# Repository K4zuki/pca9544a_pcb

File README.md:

# pca9544a_pcb
a PCB design for PCA9544A I2C MUX

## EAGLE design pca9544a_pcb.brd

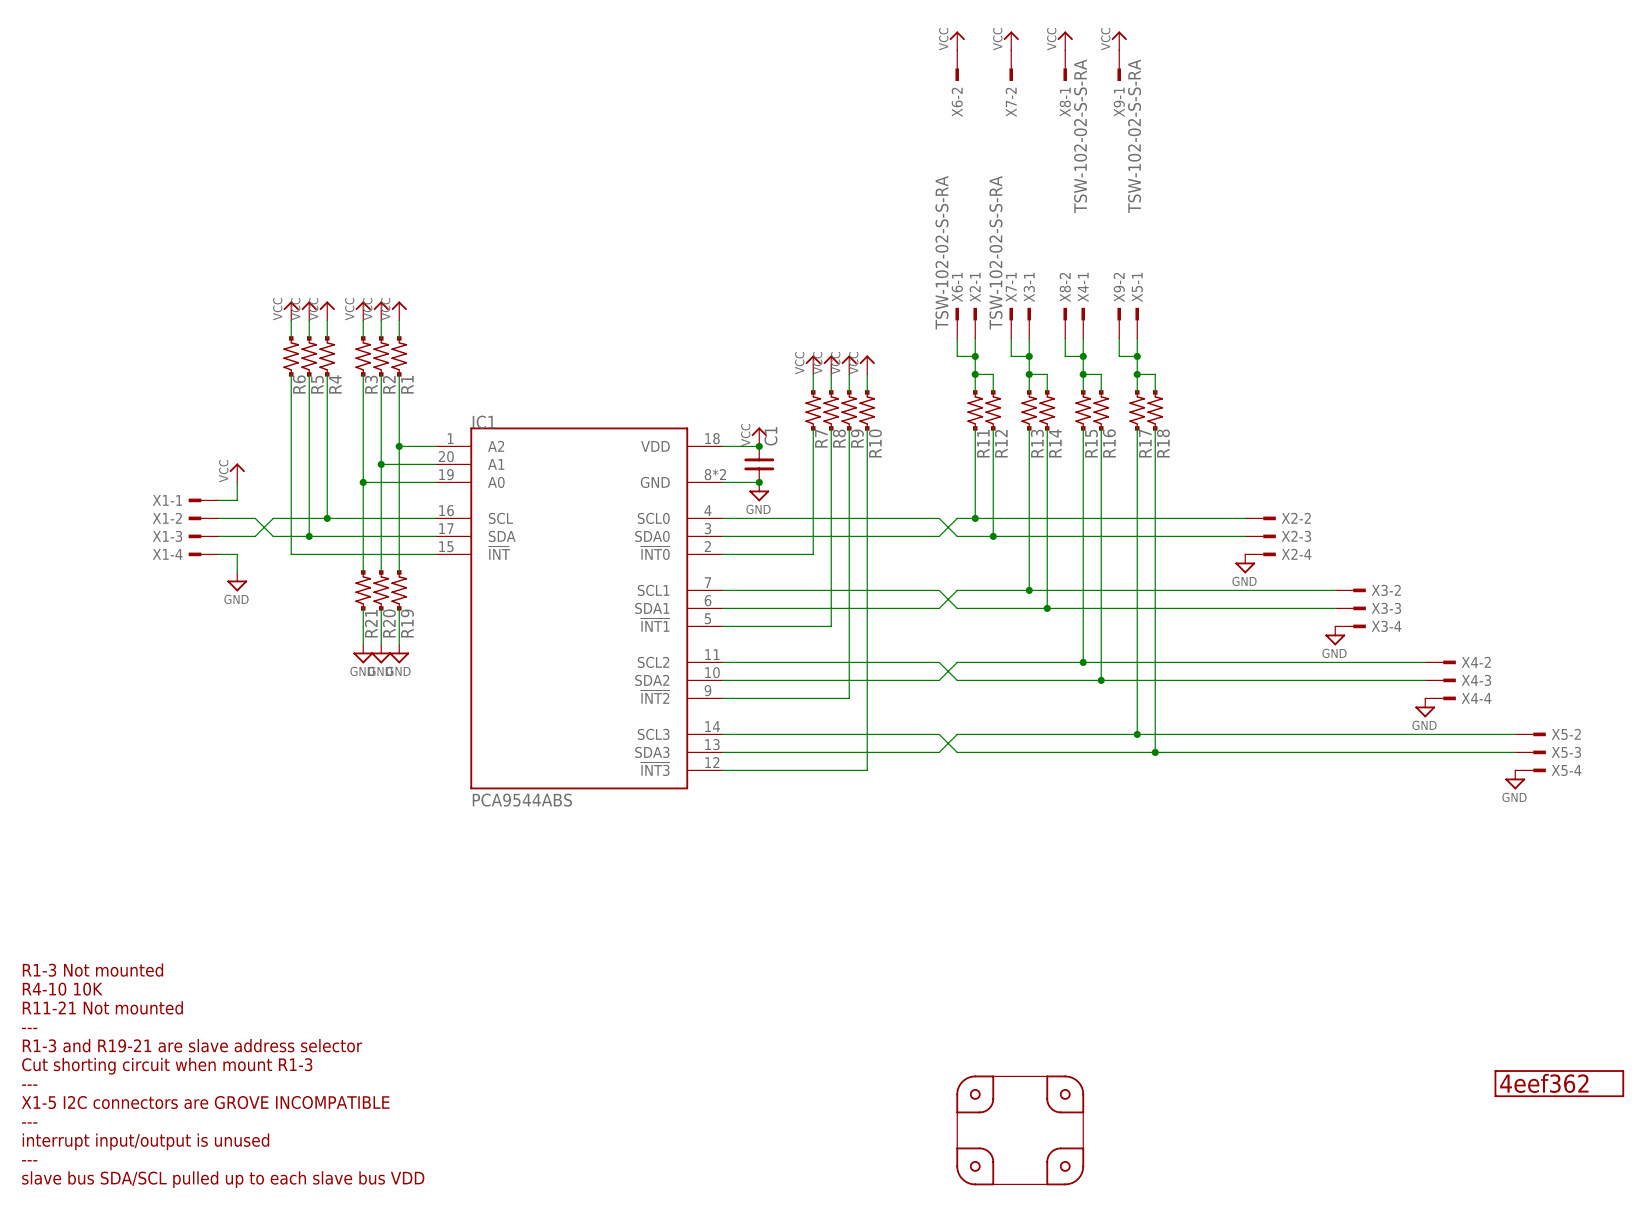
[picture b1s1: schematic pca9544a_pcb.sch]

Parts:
C1: C-SMD-0.1U-1608; CR-1608
GIT1: 4eef362; GIT-REVISION_1.2
IC1: PCA9544ABS; QFN20-0.65P5.0X5.0
P1, P2, P3, P4: PCB-CORNER
R1, R2, R3, R4, R5, R6, R7, R8, R9, R10, R11, R12, R13, R14, R15, R16, R17, R18: R-US-10K-1608; R-1608-PADPAD
R19, R20, R21: R-US--1005SHORT; R0402SHORT
X1, X2, X3, X4, X5: S4B-XH-A; S4B-XH-A(LF)(SN)
X6, X7, X8, X9: TSW-102-02-S-S-RA

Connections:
GND: C1.2, IC1.8 (GND), IC1.EP (GND), R19.1, R19.2 (1), R20.1, R20.2 (1), R21.1, R21.2 (1), X1.4, X2.4, X3.4, X4.4, X5.4
unnamed: IC1.1 (A2), R1.1, R19.3 (2)
unnamed: IC1.20 (A1), R2.1, R20.3 (2)
unnamed: IC1.19 (A0), R3.1, R21.3 (2)
unnamed: IC1.16 (SCL), R4.1, X1.3
unnamed: IC1.17 (SDA), R5.1, X1.2
unnamed: IC1.15 (!INT!), R6.1
unnamed: IC1.4 (SCL0), R12.1, X2.3
unnamed: IC1.3 (SDA0), R11.1, X2.2
unnamed: IC1.2 (!INT0!), R7.1
unnamed: IC1.7 (SCL1), R14.1, X3.3
unnamed: IC1.6 (SDA1), R13.1, X3.2
unnamed: IC1.5 (!INT1!), R8.1
unnamed: IC1.11 (SCL2), R16.1, X4.3
unnamed: IC1.10 (SDA2), R15.1, X4.2
unnamed: IC1.9 (!INT2!), R9.1
unnamed: IC1.14 (SCL3), R18.1, X5.3
unnamed: IC1.13 (SDA3), R17.1, X5.2
unnamed: IC1.12 (!INT3!), R10.1
unnamed: R11.2, R12.2, X2.1, X6.1
unnamed: R13.2, R14.2, X3.1, X7.1
unnamed: R15.2, R16.2, X4.1, X8.2
unnamed: R17.2, R18.2, X5.1, X9.2
VCC: C1.1, IC1.18 (VDD), R1.2, R2.2, R3.2, R4.2, R5.2, R6.2, R7.2, R8.2, R9.2, R10.2, X1.1, X6.2, X7.2, X8.1, X9.1

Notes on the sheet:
R1-3 Not mounted R4-10 10K R11-21 Not mounted --- R1-3 and R19-21 are slave address selector Cut shorting circuit when mount R1-3 --- X1-5 I2C connectors are GROVE INCOMPATIBLE --- interrupt input/output is unused --- slave bus SDA/SCL pulled up to each slave bus VDD

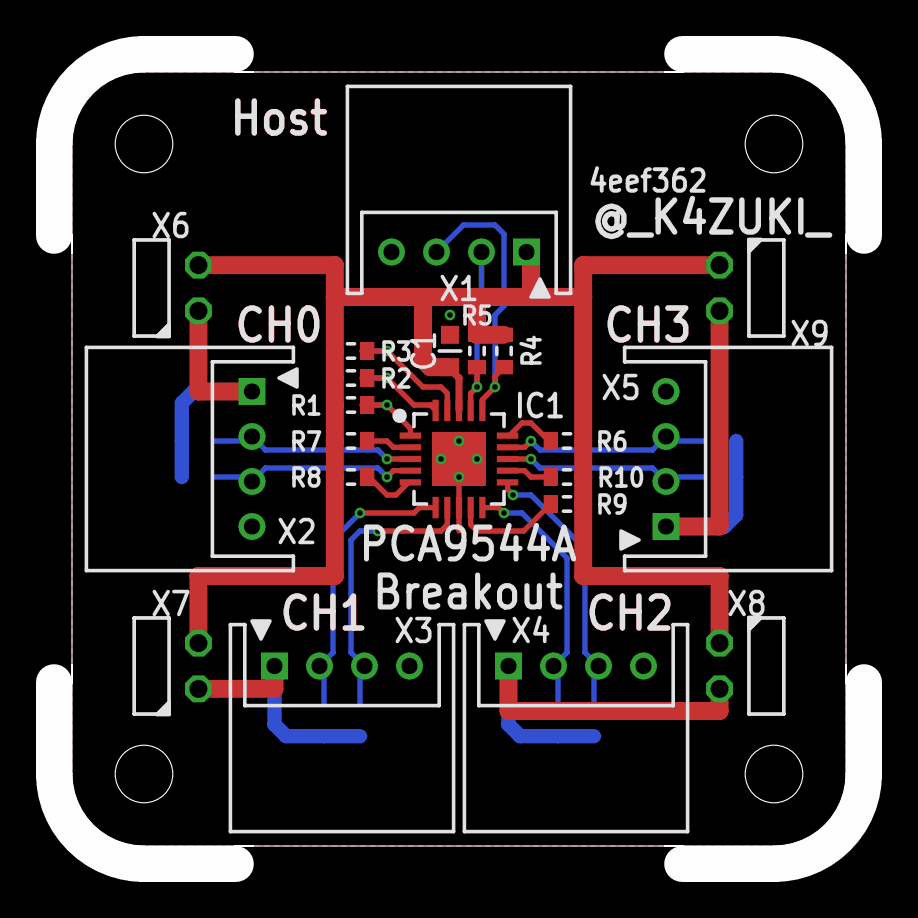
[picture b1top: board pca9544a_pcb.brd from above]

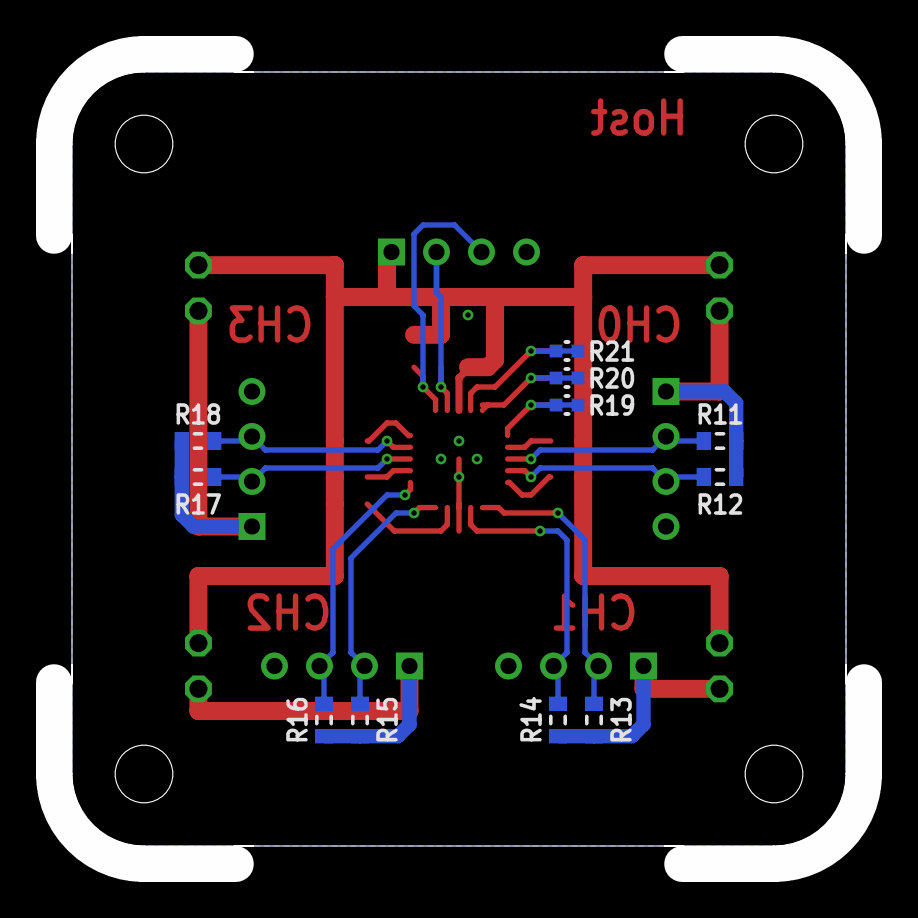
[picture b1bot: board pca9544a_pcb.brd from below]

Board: 2 copper layers, 45.0 x 45.0 mm, 37 parts (11 on the bottom side), 24 nets.

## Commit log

2018-04-04 add library as submodule
2018-04-04 update submodule lib
2018-04-04 add schematic and board files
2018-04-04 apply lib update
2018-04-07 update submodule
2018-04-08 add submodules
2018-04-08 gerber out
2018-04-19 fix layer
2018-04-20 move X1-5 to have enough area for JST XH connectors
    X1 rotated
2018-04-24 update submodule library
2018-04-24 replace X1-X5 to JST XH 4P right angle headers
2018-04-24 fix an airwire
2018-07-14 add X6~X9 to short Host VDD and each channel VDD
2018-07-14 fix silk
2018-07-14 pullups trace width changed back to 0.8mm
2018-07-14 fix X5 silk
2018-07-14 fix silk layer gerber
2018-07-14 moved X7 and X8 headers
